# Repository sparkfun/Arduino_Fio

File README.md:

Arduino Fio
========================================

[*Arduino Fio (DEV-10116)*](https://www.sparkfun.com/products/10116)

Repository Contents
-------------------
* **/Hardware** - Eagle design files (.brd, .sch)
* **/Production** - Production panel files (.brd)

License Information
-------------------

This product is _**open source**_! 

Please review the LICENSE.md file for license information. 

If you have any questions or concerns on licensing, please contact techsupport@sparkfun.com.

Distributed as-is; no warranty is given.

- Your friends at SparkFun.

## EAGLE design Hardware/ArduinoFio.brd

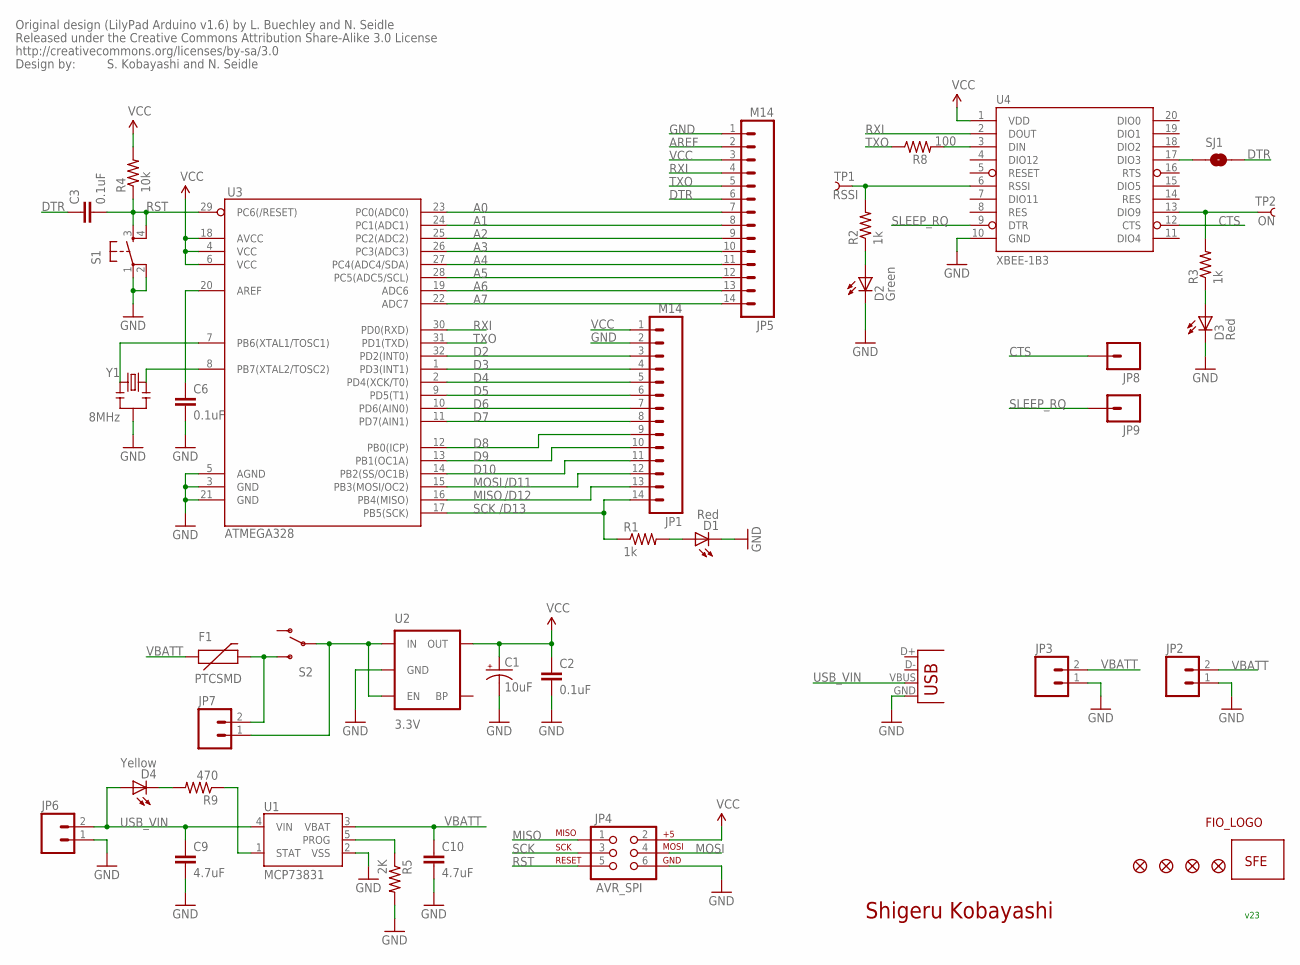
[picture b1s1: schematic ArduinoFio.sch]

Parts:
C1: 10uF; EIA3216
C2, C3, C6: 0.1uF; 0402-CAP
C9, C10: 4.7uF; 0402-CAP
D1, D3: Red; LED-0603
D2: Green; LED-0603
D4: Yellow; LED-0603
F1: PTCSMD; PTC-1206
FD1, FD2: FIDUCIAL1X2; FIDUCIAL-1X2
JP1, JP5: M14; 1X14
JP2, JP6, JP7: M02PTH; 1X02
JP3: M02-JST-2MM-SMT; JST-2-SMD
JP4: AVR_SPI; 2X3
JP8, JP9: M01PTH; 1X01
R1, R2, R3: 1k; 0402-RES
R4: 10k; 0402-RES
R5: 2K; 0402-RES
R8: 100; 0402-RES
R9: 470; 0402-RES
S1: TAC_SWITCHSMD; TACTILE_SWITCH_SMD
S2: SWITCH-SPSTSMD; AYZ0202
SJ1: SOLDERJUMPERNC; SJ_2S
TP1: RSSI; PAD.03X.05
TP2: ON; PAD.03X.05
U1: MCP73831; SOT23-5
U2: 3.3V; SOT23-5
U3: ATMEGA328; TQFP32-08
U4: XBEE-1B3; XBEE-SMD
U$1: LOGO-SFENEW; SFE-NEW-WEBLOGO
U$3: CREATIVE_COMMONS
U$4, U$5: FIDUCIAL1X2; FIDUCIAL-1X2
U$6: FIO_LOGOV2; FUNNEL_LOGO_BOTTOM_V2
X1: USBSMD; USB-MINIB
Y1: 8MHz; RESONATOR-SMD

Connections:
A0: JP5.7, U3.23 (PC0(ADC0))
A1: JP5.8, U3.24 (PC1(ADC1))
A2: JP5.9, U3.25 (PC2(ADC2))
A3: JP5.10, U3.26 (PC3(ADC3))
A4: JP5.11, U3.27 (PC4(ADC4/SDA))
A5: JP5.12, U3.28 (PC5(ADC5/SCL))
A6: JP5.13, U3.19 (ADC6)
A7: JP5.14, U3.22 (ADC7)
AREF: C6.1, JP5.2, U3.20 (AREF)
CTS: JP8.1, U4.12 (CTS)
D2: JP1.3, U3.32 (PD2(INT0))
D3: JP1.4, U3.1 (PD3(INT1))
D4: JP1.5, U3.2 (PD4(XCK/T0))
D5: JP1.6, U3.9 (PD5(T1))
D6: JP1.7, U3.10 (PD6(AIN0))
D7: JP1.8, U3.11 (PD7(AIN1))
D8: JP1.9, U3.12 (PB0(ICP))
D9: JP1.10, U3.13 (PB1(OC1A))
D10: JP1.11, U3.14 (PB2(SS/OC1B))
DTR: C3.1, JP5.6, SJ1.2
GND: C1.C (-), C2.2, C6.2, C9.2, C10.2, D1.C, D2.C, D3.C, JP1.2, JP2.1, JP3.1, JP4.6, JP5.1, JP6.1, R5.2, S1.1, S1.2, U1.2 (VSS), U2.2 (GND), U3.3 (GND), U3.5 (AGND), U3.21 (GND), U4.10 (GND), X1.GND, Y1.2
MISO: JP1.13, JP4.1, U3.16 (PB4(MISO))
MOSI: JP1.12, JP4.4, U3.15 (PB3(MOSI/OC2))
unnamed: R3.2, TP2.P$1, U4.13 (DIO9)
unnamed: D1.A, R1.2
unnamed: D2.A, R2.1
unnamed: R2.2, TP1.P$1, U4.6 (RSSI)
unnamed: JP7.1, S2.2, U2.1 (IN), U2.3 (EN)
unnamed: D3.A, R3.1
unnamed: R8.2, U4.3 (DIN)
unnamed: D4.C, R9.2
unnamed: F1.2, JP7.2, S2.3 (S)
unnamed: U3.7 (PB6(XTAL1/TOSC1)), Y1.3
unnamed: R5.1, U1.5 (PROG)
unnamed: U3.8 (PB7(XTAL2/TOSC2)), Y1.1
unnamed: SJ1.1, U4.17 (DIO3)
unnamed: R9.1, U1.1 (STAT)
RST: C3.2, JP4.5, R4.1, S1.3, S1.4, U3.29 (PC6(/RESET))
RXI: JP5.4, U3.30 (PD0(RXD)), U4.2 (DOUT)
SCK: JP1.14, JP4.3, R1.1, U3.17 (PB5(SCK))
SLEEP_RQ: JP9.1, U4.9 (DTR)
TXO: JP5.5, R8.1, U3.31 (PD1(TXD))
USB_VIN: C9.1, D4.A, JP6.2, U1.4 (VIN), X1.VBUS
VBATT: C10.1, F1.1, JP2.2, JP3.2, U1.3 (VBAT)
VCC: C1.A (+), C2.1, JP1.1, JP4.2, JP5.3, R4.2, U2.5 (OUT), U3.4 (VCC), U3.6 (VCC), U3.18 (AVCC), U4.1 (VDD)

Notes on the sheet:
Shigeru Kobayashi
/D11
/D12
/D13
Original design (LilyPad Arduino v1.6) by L. Buechley and N. Seidle
S. Kobayashi and N. Seidle
v23

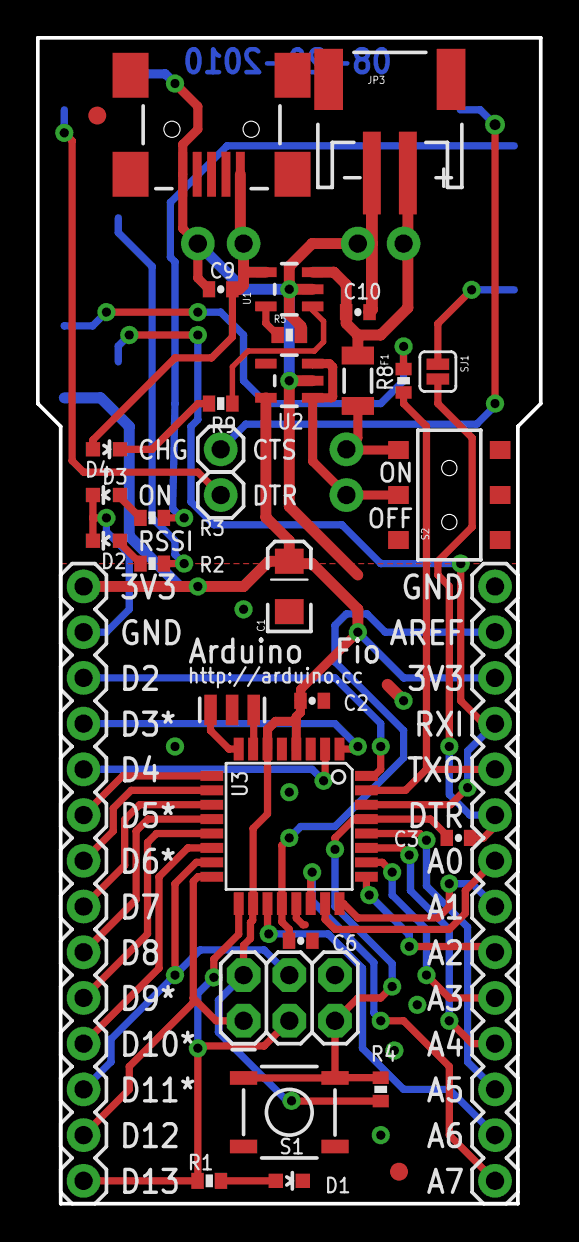
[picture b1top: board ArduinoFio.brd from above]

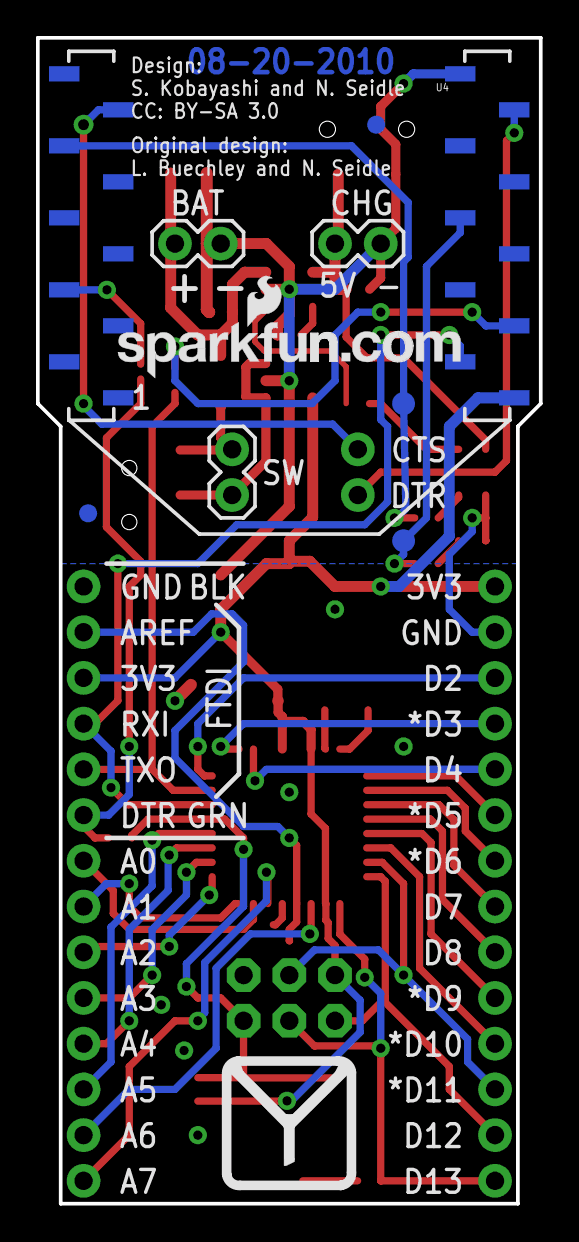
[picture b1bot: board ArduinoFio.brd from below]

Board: 2 copper layers, 27.9 x 64.8 mm, 45 parts (9 on the bottom side), 45 nets.

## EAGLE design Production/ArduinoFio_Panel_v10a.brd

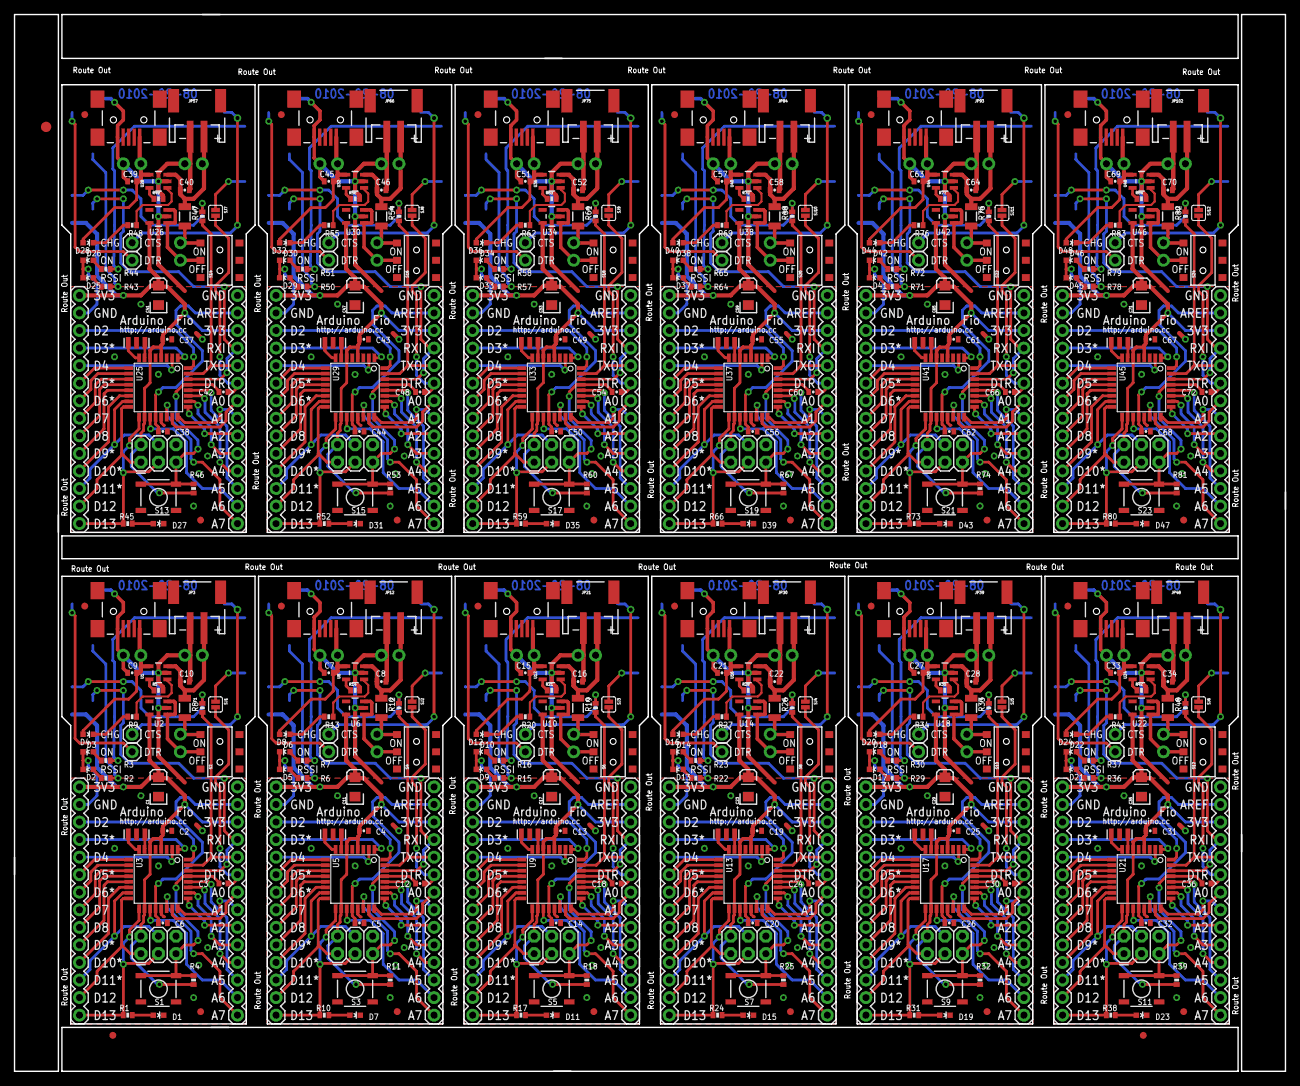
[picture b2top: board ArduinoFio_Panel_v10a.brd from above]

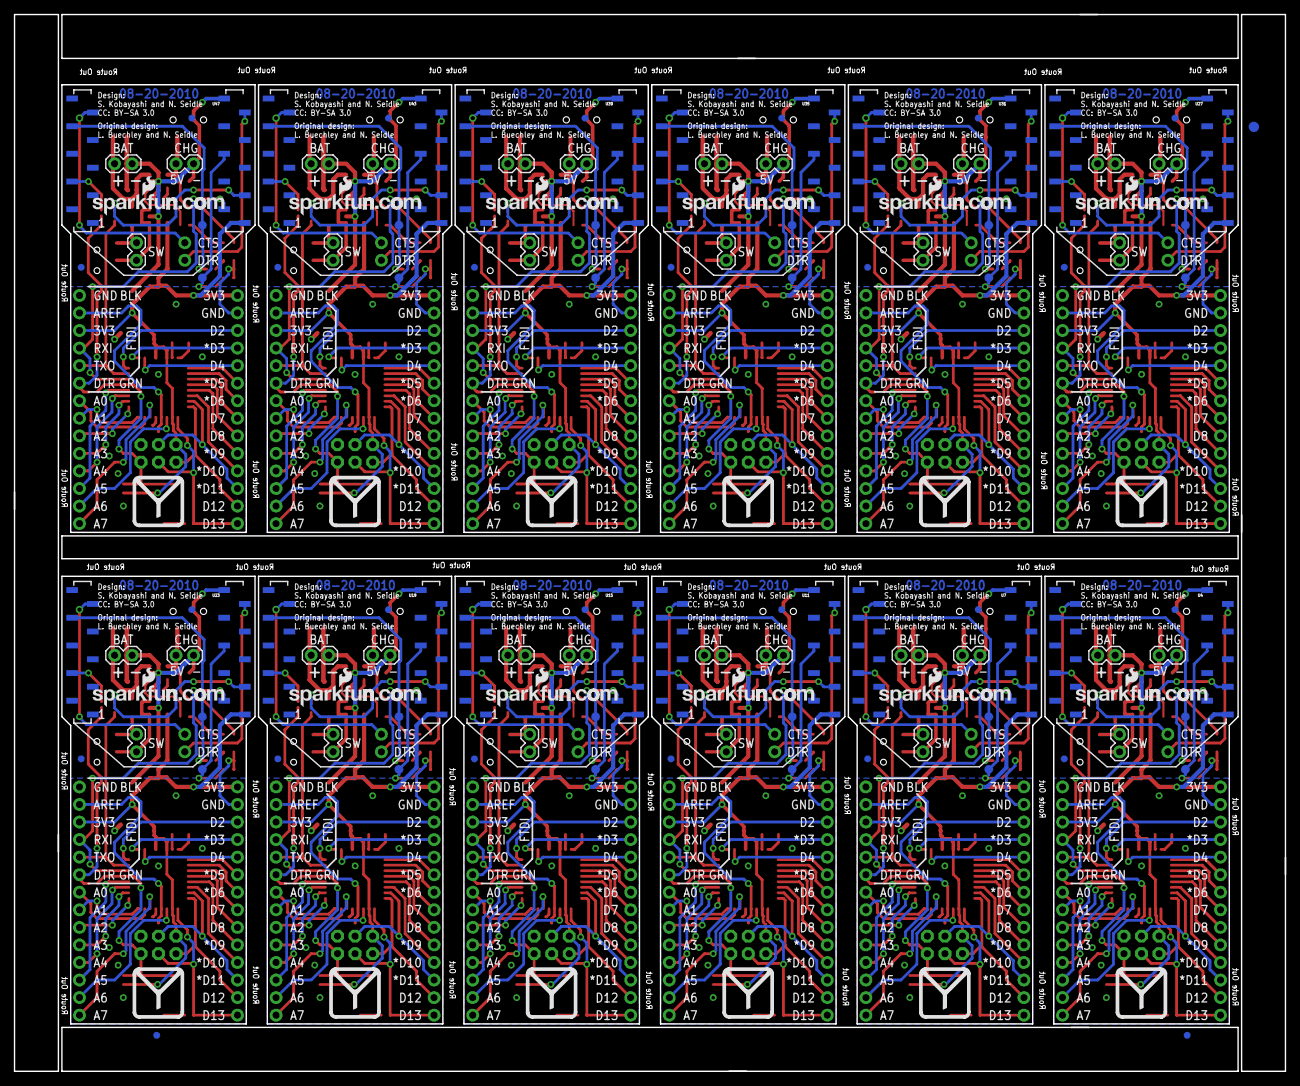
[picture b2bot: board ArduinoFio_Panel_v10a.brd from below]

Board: 2 copper layers, 183.9 x 152.9 mm, 534 parts (111 on the bottom side), 540 nets.

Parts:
C1, C11, C17, C23, C29, C35, C41, C47, C53, C59, C65, C71: 10uF; EIA3216
C2, C3, C4, C5, C6, C12, C13, C14, C18, C19, C20, C24, C25, C26, C30, C31, C32, C36, C37, C38, C42, C43, C44, C48, C49, C50, C54, C55, C56, C60, C61, C62, C66, C67, C68, C72: 0.1uF; 0402-CAP
C7, C8, C9, C10, C15, C16, C21, C22, C27, C28, C33, C34, C39, C40, C45, C46, C51, C52, C57, C58, C63, C64, C69, C70: 4.7uF; 0402-CAP
D1, D3, D6, D7, D10, D11, D14, D15, D18, D19, D22, D23, D26, D27, D30, D31, D34, D35, D38, D39, D42, D43, D46, D47: Red; LED-0603
D2, D5, D9, D13, D17, D21, D25, D29, D33, D37, D41, D45: Green; LED-0603
D4, D8, D12, D16, D20, D24, D28, D32, D36, D40, D44, D48: Yellow; LED-0603
E$1, E$2: FIDUCIAL-1.5X3
E$3, E$4, E$7, E$8: FIDUCIAL-1X2
F1, F2, F3, F4, F5, F6, F7, F8, F9, F10, F11, F12: PTCSMD; PTC-1206
FD1, FD2, FD3, FD4, FD5, FD6, FD7, FD8, FD9, FD10, FD11, FD12, FD13, FD14, FD15, FD16, FD17, FD18, FD19, FD20, FD21, FD22, FD23, FD24: FIDUCIAL1X2; FIDUCIAL-1X2
JP1, JP5, JP11, JP13, JP20, JP22, JP29, JP31, JP38, JP40, JP47, JP49, JP56, JP58, JP65, JP67, JP74, JP76, JP83, JP85, JP92, JP94, JP101, JP103: M14; 1X14
JP2, JP6, JP7, JP14, JP15, JP16, JP23, JP24, JP25, JP32, JP33, JP34, JP41, JP42, JP43, JP50, JP51, JP52, JP59, JP60, JP61, JP68, JP69, JP70, JP77, JP78, JP79, JP86, JP87, JP88, JP95, JP96, JP97, JP104, JP105, JP106: 1X02
JP3, JP12, JP21, JP30, JP39, JP48, JP57, JP66, JP75, JP84, JP93, JP102: JST-2-SMD
JP4, JP10, JP19, JP28, JP37, JP46, JP55, JP64, JP73, JP82, JP91, JP100: AVR_SPI; 2X3
JP8, JP9, JP17, JP18, JP26, JP27, JP35, JP36, JP44, JP45, JP53, JP54, JP62, JP63, JP71, JP72, JP80, JP81, JP89, JP90, JP98, JP99, JP107, JP108: 1X01
R1, R2, R3, R6, R7, R10, R15, R16, R17, R22, R23, R24, R29, R30, R31, R36, R37, R38, R43, R44, R45, R50, R51, R52, R57, R58, R59, R64, R65, R66, R71, R72, R73, R78, R79, R80: 1k; 0402-RES
R4, R11, R18, R25, R32, R39, R46, R53, R60, R67, R74, R81: 10k; 0402-RES
R5, R14, R21, R28, R35, R42, R49, R56, R63, R70, R77, R84: 2K; 0402-RES
R8, R12, R19, R26, R33, R40, R47, R54, R61, R68, R75, R82: 100; 0402-RES
R9, R13, R20, R27, R34, R41, R48, R55, R62, R69, R76, R83: 470; 0402-RES
S1, S3, S5, S7, S9, S11, S13, S15, S17, S19, S21, S23: TACTILE_SWITCH_SMD
S2, S4, S6, S8, S10, S12, S14, S16, S18, S20, S22, S24: AYZ0202
SJ1, SJ2, SJ3, SJ4, SJ5, SJ6, SJ7, SJ8, SJ9, SJ10, SJ11, SJ12: SOLDERJUMPERNC; SJ_2S
TP1, TP3, TP5, TP7, TP9, TP11, TP13, TP15, TP17, TP19, TP21, TP23: RSSI; PAD.03X.05
TP2, TP4, TP6, TP8, TP10, TP12, TP14, TP16, TP18, TP20, TP22, TP24: ON; PAD.03X.05
U1, U8, U12, U16, U20, U24, U28, U32, U36, U40, U44, U48: MCP73831; SOT23-5
U2, U6, U10, U14, U18, U22, U26, U30, U34, U38, U42, U46: 3.3V; SOT23-5
U3, U5, U9, U13, U17, U21, U25, U29, U33, U37, U41, U45: ATMEGA328; TQFP32-08
U4, U7, U11, U15, U19, U23, U27, U31, U35, U39, U43, U47: XBEE-1B3; XBEE-SMD
U$1, U$2, U$9, U$13, U$17, U$21, U$25, U$29, U$33, U$37, U$41, U$45: LOGO-SFENEW; SFE-NEW-WEBLOGO
U$3, U$4, U$5, U$7, U$10, U$11, U$14, U$15, U$18, U$19, U$22, U$23, U$26, U$27, U$30, U$31, U$34, U$35, U$38, U$39, U$42, U$43, U$46, U$47: FIDUCIAL1X2; FIDUCIAL-1X2
U$6, U$8, U$12, U$16, U$20, U$24, U$28, U$32, U$36, U$40, U$44, U$48: FIO_LOGOV2; FUNNEL_LOGO_BOTTOM_V2
X1, X2, X3, X4, X5, X6, X7, X8, X9, X10, X11, X12: USBSMD; USB-MINIB
Y1, Y2, Y3, Y4, Y5, Y6, Y7, Y8, Y9, Y10, Y11, Y12: 8MHz; RESONATOR-SMD

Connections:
A0: JP5.7, U3.23
A1: JP5.8, U3.24
A2: JP5.9, U3.25
A3: JP5.10, U3.26
A4: JP5.11, U3.27
A5: JP5.12, U3.28
A6: JP5.13, U3.19
A7: JP5.14, U3.22
A8: JP13.7, U5.23
A9: JP13.8, U5.24
A10: JP13.9, U5.25
A11: JP13.10, U5.26
A12: JP13.11, U5.27
A13: JP13.12, U5.28
A14: JP13.13, U5.19
A15: JP13.14, U5.22
A16: JP22.7, U9.23
A17: JP22.8, U9.24
A18: JP22.9, U9.25
A19: JP22.10, U9.26
A20: JP22.11, U9.27
A21: JP22.12, U9.28
A22: JP22.13, U9.19
A23: JP22.14, U9.22
A24: JP31.7, U13.23
A25: JP31.8, U13.24
A26: JP31.9, U13.25
A27: JP31.10, U13.26
A28: JP31.11, U13.27
A29: JP31.12, U13.28
A30: JP31.13, U13.19
A31: JP31.14, U13.22
A32: JP40.7, U17.23
A33: JP40.8, U17.24
A34: JP40.9, U17.25
A35: JP40.10, U17.26
A36: JP40.11, U17.27
A37: JP40.12, U17.28
A38: JP40.13, U17.19
A39: JP40.14, U17.22
A40: JP49.7, U21.23
A41: JP49.8, U21.24
A42: JP49.9, U21.25
A43: JP49.10, U21.26
A44: JP49.11, U21.27
A45: JP49.12, U21.28
A46: JP49.13, U21.19
A47: JP49.14, U21.22
A48: JP58.7, U25.23
A49: JP58.8, U25.24
A50: JP58.9, U25.25
A51: JP58.10, U25.26
A52: JP58.11, U25.27
A53: JP58.12, U25.28
A54: JP58.13, U25.19
A55: JP58.14, U25.22
A56: JP67.7, U29.23
A57: JP67.8, U29.24
A58: JP67.9, U29.25
A59: JP67.10, U29.26
A60: JP67.11, U29.27
A61: JP67.12, U29.28
A62: JP67.13, U29.19
A63: JP67.14, U29.22
A64: JP76.7, U33.23
A65: JP76.8, U33.24
A66: JP76.9, U33.25
A67: JP76.10, U33.26
A68: JP76.11, U33.27
A69: JP76.12, U33.28
A70: JP76.13, U33.19
A71: JP76.14, U33.22
A72: JP85.7, U37.23
A73: JP85.8, U37.24
A74: JP85.9, U37.25
A75: JP85.10, U37.26
A76: JP85.11, U37.27
A77: JP85.12, U37.28
A78: JP85.13, U37.19
A79: JP85.14, U37.22
A80: JP94.7, U41.23
A81: JP94.8, U41.24
A82: JP94.9, U41.25
A83: JP94.10, U41.26
A84: JP94.11, U41.27
A85: JP94.12, U41.28
A86: JP94.13, U41.19
A87: JP94.14, U41.22
A88: JP103.7, U45.23
A89: JP103.8, U45.24
A90: JP103.9, U45.25
A91: JP103.10, U45.26
A92: JP103.11, U45.27
A93: JP103.12, U45.28
A94: JP103.13, U45.19
A95: JP103.14, U45.22
AREF: C6.1, JP5.2, U3.20
AREF1: C5.1, JP13.2, U5.20
AREF2: C14.1, JP22.2, U9.20
AREF3: C20.1, JP31.2, U13.20
AREF4: C26.1, JP40.2, U17.20
AREF5: C32.1, JP49.2, U21.20
AREF6: C38.1, JP58.2, U25.20
AREF7: C44.1, JP67.2, U29.20
AREF8: C50.1, JP76.2, U33.20
AREF9: C56.1, JP85.2, U37.20
AREF10: C62.1, JP94.2, U41.20
AREF11: C68.1, JP103.2, U45.20
CTS: JP8.1, U4.12
CTS1: JP17.1, U7.12
CTS2: JP26.1, U11.12
CTS3: JP35.1, U15.12
CTS4: JP44.1, U19.12
CTS5: JP53.1, U23.12
CTS6: JP62.1, U27.12
CTS7: JP71.1, U31.12
CTS8: JP80.1, U35.12
CTS9: JP89.1, U39.12
CTS10: JP98.1, U43.12
CTS11: JP107.1, U47.12
D1: JP11.3, U5.32
D2: JP1.3, U3.32
D3: JP1.4, U3.1
D4: JP1.5, U3.2
D5: JP1.6, U3.9
D6: JP1.7, U3.10
D7: JP1.8, U3.11
D8: JP1.9, U3.12
D9: JP1.10, U3.13
D10: JP1.11, U3.14
D11: JP11.4, U5.1
D12: JP11.5, U5.2
D13: JP11.6, U5.9
D14: JP11.7, U5.10
D15: JP11.9, U5.12
D16: JP11.11, U5.14
D17: JP11.8, U5.11
D18: JP11.10, U5.13
D19: JP20.3, U9.32
D20: JP20.4, U9.1
D21: JP20.5, U9.2
D22: JP20.6, U9.9
D23: JP20.7, U9.10
D24: JP20.9, U9.12
D25: JP20.11, U9.14
D26: JP20.8, U9.11
D27: JP20.10, U9.13
D28: JP29.3, U13.32
D29: JP29.4, U13.1
D30: JP29.5, U13.2
D31: JP29.6, U13.9
D32: JP29.7, U13.10
D33: JP29.9, U13.12
D34: JP29.11, U13.14
D35: JP29.8, U13.11
D36: JP29.10, U13.13
D37: JP38.3, U17.32
D38: JP38.4, U17.1
D39: JP38.5, U17.2
D40: JP38.6, U17.9
D41: JP38.7, U17.10
D42: JP38.9, U17.12
D43: JP38.11, U17.14
D44: JP38.8, U17.11
D45: JP38.10, U17.13
D46: JP47.3, U21.32
D47: JP47.4, U21.1
D48: JP47.5, U21.2
D49: JP47.6, U21.9
D50: JP47.7, U21.10
D51: JP47.9, U21.12
D52: JP47.11, U21.14
D53: JP47.8, U21.11
D54: JP47.10, U21.13
D55: JP56.3, U25.32
D56: JP56.4, U25.1
D57: JP56.5, U25.2
D58: JP56.6, U25.9
D59: JP56.7, U25.10
D60: JP56.9, U25.12
D61: JP56.11, U25.14
D62: JP56.8, U25.11
D63: JP56.10, U25.13
D64: JP65.3, U29.32
D65: JP65.4, U29.1
D66: JP65.5, U29.2
D67: JP65.6, U29.9
D68: JP65.7, U29.10
D69: JP65.9, U29.12
D70: JP65.11, U29.14
D71: JP65.8, U29.11
D72: JP65.10, U29.13
D73: JP74.3, U33.32
D74: JP74.4, U33.1
D75: JP74.5, U33.2
D76: JP74.6, U33.9
D77: JP74.7, U33.10
D78: JP74.9, U33.12
D79: JP74.11, U33.14
D80: JP74.8, U33.11
D81: JP74.10, U33.13
D82: JP83.3, U37.32
D83: JP83.4, U37.1
D84: JP83.5, U37.2
D85: JP83.6, U37.9
D86: JP83.7, U37.10
D87: JP83.9, U37.12
D88: JP83.11, U37.14
D89: JP83.8, U37.11
D90: JP83.10, U37.13
D91: JP92.3, U41.32
D92: JP92.4, U41.1
D93: JP92.5, U41.2
D94: JP92.6, U41.9
D95: JP92.7, U41.10
D96: JP92.9, U41.12
D97: JP92.11, U41.14
D98: JP92.8, U41.11
D99: JP92.10, U41.13
D100: JP101.3, U45.32
D101: JP101.4, U45.1
D102: JP101.5, U45.2
D103: JP101.6, U45.9
D104: JP101.7, U45.10
D105: JP101.9, U45.12
D106: JP101.11, U45.14
D107: JP101.8, U45.11
D108: JP101.10, U45.13
DTR: C3.1, JP5.6, SJ1.2
DTR1: C12.1, JP13.6, SJ2.2
DTR2: C18.1, JP22.6, SJ3.2
DTR3: C24.1, JP31.6, SJ4.2
DTR4: C30.1, JP40.6, SJ5.2
DTR5: C36.1, JP49.6, SJ6.2
DTR6: C42.1, JP58.6, SJ7.2
DTR7: C48.1, JP67.6, SJ8.2
DTR8: C54.1, JP76.6, SJ9.2
DTR9: C60.1, JP85.6, SJ10.2
DTR10: C66.1, JP94.6, SJ11.2
DTR11: C72.1, JP103.6, SJ12.2
GND: C1.C, C2.2, C6.2, C9.2, C10.2, D1.C, D2.C, D3.C, JP1.2, JP2.1, JP3.1, JP4.6, JP5.1, JP6.1, R5.2, S1.1, S1.2, U1.2, U2.2, U3.3, U3.5, U3.21, U4.10, X1.GND, Y1.2
GND1: C4.2, C5.2, C7.2, C8.2, C11.C, D5.C, D6.C, D7.C, JP10.6, JP11.2, JP12.1, JP13.1, JP14.1, JP15.1, R14.2, S3.1, S3.2, U5.3, U5.5, U5.21, U6.2, U7.10, U8.2, X2.GND, Y2.2
GND2: C13.2, C14.2, C15.2, C16.2, C17.C, D9.C, D10.C, D11.C, JP19.6, JP20.2, JP21.1, JP22.1, JP23.1, JP24.1, R21.2, S5.1, S5.2, U9.3, U9.5, U9.21, U10.2, U11.10, U12.2, X3.GND, Y3.2
GND3: C19.2, C20.2, C21.2, C22.2, C23.C, D13.C, D14.C, D15.C, JP28.6, JP29.2, JP30.1, JP31.1, JP32.1, JP33.1, R28.2, S7.1, S7.2, U13.3, U13.5, U13.21, U14.2, U15.10, U16.2, X4.GND, Y4.2
GND4: C25.2, C26.2, C27.2, C28.2, C29.C, D17.C, D18.C, D19.C, JP37.6, JP38.2, JP39.1, JP40.1, JP41.1, JP42.1, R35.2, S9.1, S9.2, U17.3, U17.5, U17.21, U18.2, U19.10, U20.2, X5.GND, Y5.2
GND5: C31.2, C32.2, C33.2, C34.2, C35.C, D21.C, D22.C, D23.C, JP46.6, JP47.2, JP48.1, JP49.1, JP50.1, JP51.1, R42.2, S11.1, S11.2, U21.3, U21.5, U21.21, U22.2, U23.10, U24.2, X6.GND, Y6.2
GND6: C37.2, C38.2, C39.2, C40.2, C41.C, D25.C, D26.C, D27.C, JP55.6, JP56.2, JP57.1, JP58.1, JP59.1, JP60.1, R49.2, S13.1, S13.2, U25.3, U25.5, U25.21, U26.2, U27.10, U28.2, X7.GND, Y7.2
GND7: C43.2, C44.2, C45.2, C46.2, C47.C, D29.C, D30.C, D31.C, JP64.6, JP65.2, JP66.1, JP67.1, JP68.1, JP69.1, R56.2, S15.1, S15.2, U29.3, U29.5, U29.21, U30.2, U31.10, U32.2, X8.GND, Y8.2
GND8: C49.2, C50.2, C51.2, C52.2, C53.C, D33.C, D34.C, D35.C, JP73.6, JP74.2, JP75.1, JP76.1, JP77.1, JP78.1, R63.2, S17.1, S17.2, U33.3, U33.5, U33.21, U34.2, U35.10, U36.2, X9.GND, Y9.2
GND9: C55.2, C56.2, C57.2, C58.2, C59.C, D37.C, D38.C, D39.C, JP82.6, JP83.2, JP84.1, JP85.1, JP86.1, JP87.1, R70.2, S19.1, S19.2, U37.3, U37.5, U37.21, U38.2, U39.10, U40.2, X10.GND, Y10.2
GND10: C61.2, C62.2, C63.2, C64.2, C65.C, D41.C, D42.C, D43.C, JP91.6, JP92.2, JP93.1, JP94.1, JP95.1, JP96.1, R77.2, S21.1, S21.2, U41.3, U41.5, U41.21, U42.2, U43.10, U44.2, X11.GND, Y11.2
GND11: C67.2, C68.2, C69.2, C70.2, C71.C, D45.C, D46.C, D47.C, JP100.6, JP101.2, JP102.1, JP103.1, JP104.1, JP105.1, R84.2, S23.1, S23.2, U45.3, U45.5, U45.21, U46.2, U47.10, U48.2, X12.GND, Y12.2
MISO: JP1.13, JP4.1, U3.16
MISO1: JP10.1, JP11.13, U5.16
MISO2: JP19.1, JP20.13, U9.16
MISO3: JP28.1, JP29.13, U13.16
MISO4: JP37.1, JP38.13, U17.16
MISO5: JP46.1, JP47.13, U21.16
MISO6: JP55.1, JP56.13, U25.16
MISO7: JP64.1, JP65.13, U29.16
MISO8: JP73.1, JP74.13, U33.16
MISO9: JP82.1, JP83.13, U37.16
MISO10: JP91.1, JP92.13, U41.16
MISO11: JP100.1, JP101.13, U45.16
MOSI: JP1.12, JP4.4, U3.15
MOSI1: JP10.4, JP11.12, U5.15
MOSI2: JP19.4, JP20.12, U9.15
MOSI3: JP28.4, JP29.12, U13.15
MOSI4: JP37.4, JP38.12, U17.15
MOSI5: JP46.4, JP47.12, U21.15
MOSI6: JP55.4, JP56.12, U25.15
MOSI7: JP64.4, JP65.12, U29.15
MOSI8: JP73.4, JP74.12, U33.15
MOSI9: JP82.4, JP83.12, U37.15
MOSI10: JP91.4, JP92.12, U41.15
MOSI11: JP100.4, JP101.12, U45.15
unnamed: R3.2, TP2.P$1, U4.13
unnamed: D1.A, R1.2
unnamed: D2.A, R2.1
unnamed: R2.2, TP1.P$1, U4.6
unnamed: JP7.1, S2.2, U2.1, U2.3
unnamed: D3.A, R3.1
unnamed: R8.2, U4.3
unnamed: D4.C, R9.2
unnamed: F1.2, JP7.2, S2.3
unnamed: U3.7, Y1.3
unnamed: R5.1, U1.5
unnamed: U3.8, Y1.1
unnamed: SJ1.1, U4.17
unnamed: R9.1, U1.1
unnamed: D5.A, R6.1
unnamed: R6.2, TP3.P$1, U7.6
unnamed: D6.A, R7.1
unnamed: R7.2, TP4.P$1, U7.13
unnamed: U5.7, Y2.3
unnamed: U5.8, Y2.1
unnamed: D7.A, R10.2
unnamed: R12.2, U7.3
unnamed: JP16.1, S4.2, U6.1, U6.3
unnamed: F2.2, JP16.2, S4.3
unnamed: SJ2.1, U7.17
unnamed: R14.1, U8.5
unnamed: R13.1, U8.1
unnamed: D8.C, R13.2
unnamed: D9.A, R15.1
unnamed: R15.2, TP5.P$1, U11.6
unnamed: D10.A, R16.1
unnamed: R16.2, TP6.P$1, U11.13
unnamed: U9.7, Y3.3
unnamed: U9.8, Y3.1
unnamed: D11.A, R17.2
unnamed: R19.2, U11.3
unnamed: JP25.1, S6.2, U10.1, U10.3
unnamed: F3.2, JP25.2, S6.3
unnamed: SJ3.1, U11.17
unnamed: R21.1, U12.5
unnamed: R20.1, U12.1
unnamed: D12.C, R20.2
unnamed: D13.A, R22.1
unnamed: R22.2, TP7.P$1, U15.6
unnamed: D14.A, R23.1
unnamed: R23.2, TP8.P$1, U15.13
unnamed: U13.7, Y4.3
unnamed: U13.8, Y4.1
unnamed: D15.A, R24.2
unnamed: R26.2, U15.3
unnamed: JP34.1, S8.2, U14.1, U14.3
unnamed: F4.2, JP34.2, S8.3
unnamed: SJ4.1, U15.17
unnamed: R28.1, U16.5
unnamed: R27.1, U16.1
unnamed: D16.C, R27.2
unnamed: D17.A, R29.1
unnamed: R29.2, TP9.P$1, U19.6
unnamed: D18.A, R30.1
unnamed: R30.2, TP10.P$1, U19.13
unnamed: U17.7, Y5.3
unnamed: U17.8, Y5.1
unnamed: D19.A, R31.2
unnamed: R33.2, U19.3
unnamed: JP43.1, S10.2, U18.1, U18.3
unnamed: F5.2, JP43.2, S10.3
unnamed: SJ5.1, U19.17
unnamed: R35.1, U20.5
unnamed: R34.1, U20.1
unnamed: D20.C, R34.2
unnamed: D21.A, R36.1
unnamed: R36.2, TP11.P$1, U23.6
unnamed: D22.A, R37.1
unnamed: R37.2, TP12.P$1, U23.13
unnamed: U21.7, Y6.3
unnamed: U21.8, Y6.1
unnamed: D23.A, R38.2
unnamed: R40.2, U23.3
unnamed: JP52.1, S12.2, U22.1, U22.3
unnamed: F6.2, JP52.2, S12.3
unnamed: SJ6.1, U23.17
unnamed: R42.1, U24.5
unnamed: R41.1, U24.1
unnamed: D24.C, R41.2
unnamed: D25.A, R43.1
unnamed: R43.2, TP13.P$1, U27.6
unnamed: D26.A, R44.1
unnamed: R44.2, TP14.P$1, U27.13
unnamed: U25.7, Y7.3
unnamed: U25.8, Y7.1
unnamed: D27.A, R45.2
unnamed: R47.2, U27.3
unnamed: JP61.1, S14.2, U26.1, U26.3
unnamed: F7.2, JP61.2, S14.3
unnamed: SJ7.1, U27.17
unnamed: R49.1, U28.5
unnamed: R48.1, U28.1
unnamed: D28.C, R48.2
unnamed: D29.A, R50.1
unnamed: R50.2, TP15.P$1, U31.6
unnamed: D30.A, R51.1
unnamed: R51.2, TP16.P$1, U31.13
unnamed: U29.7, Y8.3
unnamed: U29.8, Y8.1
unnamed: D31.A, R52.2
unnamed: R54.2, U31.3
unnamed: JP70.1, S16.2, U30.1, U30.3
unnamed: F8.2, JP70.2, S16.3
unnamed: SJ8.1, U31.17
unnamed: R56.1, U32.5
unnamed: R55.1, U32.1
unnamed: D32.C, R55.2
unnamed: D33.A, R57.1
unnamed: R57.2, TP17.P$1, U35.6
unnamed: D34.A, R58.1
unnamed: R58.2, TP18.P$1, U35.13
unnamed: U33.7, Y9.3
unnamed: U33.8, Y9.1
unnamed: D35.A, R59.2
unnamed: R61.2, U35.3
unnamed: JP79.1, S18.2, U34.1, U34.3
unnamed: F9.2, JP79.2, S18.3
unnamed: SJ9.1, U35.17
unnamed: R63.1, U36.5
unnamed: R62.1, U36.1
unnamed: D36.C, R62.2
unnamed: D37.A, R64.1
unnamed: R64.2, TP19.P$1, U39.6
unnamed: D38.A, R65.1
unnamed: R65.2, TP20.P$1, U39.13
unnamed: U37.7, Y10.3
unnamed: U37.8, Y10.1
unnamed: D39.A, R66.2
unnamed: R68.2, U39.3
unnamed: JP88.1, S20.2, U38.1, U38.3
unnamed: F10.2, JP88.2, S20.3
unnamed: SJ10.1, U39.17
unnamed: R70.1, U40.5
unnamed: R69.1, U40.1
unnamed: D40.C, R69.2
unnamed: D41.A, R71.1
unnamed: R71.2, TP21.P$1, U43.6
unnamed: D42.A, R72.1
unnamed: R72.2, TP22.P$1, U43.13
unnamed: U41.7, Y11.3
unnamed: U41.8, Y11.1
unnamed: D43.A, R73.2
unnamed: R75.2, U43.3
unnamed: JP97.1, S22.2, U42.1, U42.3
unnamed: F11.2, JP97.2, S22.3
unnamed: SJ11.1, U43.17
unnamed: R77.1, U44.5
unnamed: R76.1, U44.1
unnamed: D44.C, R76.2
unnamed: D45.A, R78.1
unnamed: R78.2, TP23.P$1, U47.6
unnamed: D46.A, R79.1
unnamed: R79.2, TP24.P$1, U47.13
unnamed: U45.7, Y12.3
unnamed: U45.8, Y12.1
unnamed: D47.A, R80.2
unnamed: R82.2, U47.3
unnamed: JP106.1, S24.2, U46.1, U46.3
unnamed: F12.2, JP106.2, S24.3
unnamed: SJ12.1, U47.17
unnamed: R84.1, U48.5
unnamed: R83.1, U48.1
unnamed: D48.C, R83.2
RST: C3.2, JP4.5, R4.1, S1.3, S1.4, U3.29
RST1: C12.2, JP10.5, R11.1, S3.3, S3.4, U5.29
RST2: C18.2, JP19.5, R18.1, S5.3, S5.4, U9.29
RST3: C24.2, JP28.5, R25.1, S7.3, S7.4, U13.29
RST4: C30.2, JP37.5, R32.1, S9.3, S9.4, U17.29
RST5: C36.2, JP46.5, R39.1, S11.3, S11.4, U21.29
RST6: C42.2, JP55.5, R46.1, S13.3, S13.4, U25.29
RST7: C48.2, JP64.5, R53.1, S15.3, S15.4, U29.29
RST8: C54.2, JP73.5, R60.1, S17.3, S17.4, U33.29
RST9: C60.2, JP82.5, R67.1, S19.3, S19.4, U37.29
RST10: C66.2, JP91.5, R74.1, S21.3, S21.4, U41.29
RST11: C72.2, JP100.5, R81.1, S23.3, S23.4, U45.29
RXI: JP5.4, U3.30, U4.2
RXI1: JP13.4, U5.30, U7.2
RXI2: JP22.4, U9.30, U11.2
RXI3: JP31.4, U13.30, U15.2
RXI4: JP40.4, U17.30, U19.2
RXI5: JP49.4, U21.30, U23.2
RXI6: JP58.4, U25.30, U27.2
RXI7: JP67.4, U29.30, U31.2
RXI8: JP76.4, U33.30, U35.2
RXI9: JP85.4, U37.30, U39.2
RXI10: JP94.4, U41.30, U43.2
RXI11: JP103.4, U45.30, U47.2
SCK: JP1.14, JP4.3, R1.1, U3.17
SCK1: JP10.3, JP11.14, R10.1, U5.17
SCK2: JP19.3, JP20.14, R17.1, U9.17
SCK3: JP28.3, JP29.14, R24.1, U13.17
SCK4: JP37.3, JP38.14, R31.1, U17.17
SCK5: JP46.3, JP47.14, R38.1, U21.17
SCK6: JP55.3, JP56.14, R45.1, U25.17
SCK7: JP64.3, JP65.14, R52.1, U29.17
SCK8: JP73.3, JP74.14, R59.1, U33.17
SCK9: JP82.3, JP83.14, R66.1, U37.17
SCK10: JP91.3, JP92.14, R73.1, U41.17
SCK11: JP100.3, JP101.14, R80.1, U45.17
SLEEP_RQ: JP9.1, U4.9
SLEEP_RQ1: JP18.1, U7.9
SLEEP_RQ2: JP27.1, U11.9
SLEEP_RQ3: JP36.1, U15.9
SLEEP_RQ4: JP45.1, U19.9
SLEEP_RQ5: JP54.1, U23.9
SLEEP_RQ6: JP63.1, U27.9
SLEEP_RQ7: JP72.1, U31.9
SLEEP_RQ8: JP81.1, U35.9
SLEEP_RQ9: JP90.1, U39.9
SLEEP_RQ10: JP99.1, U43.9
SLEEP_RQ11: JP108.1, U47.9
TXO: JP5.5, R8.1, U3.31
TXO1: JP13.5, R12.1, U5.31
TXO2: JP22.5, R19.1, U9.31
TXO3: JP31.5, R26.1, U13.31
TXO4: JP40.5, R33.1, U17.31
TXO5: JP49.5, R40.1, U21.31
TXO6: JP58.5, R47.1, U25.31
TXO7: JP67.5, R54.1, U29.31
TXO8: JP76.5, R61.1, U33.31
TXO9: JP85.5, R68.1, U37.31
TXO10: JP94.5, R75.1, U41.31
TXO11: JP103.5, R82.1, U45.31
USB_VIN: C9.1, D4.A, JP6.2, U1.4, X1.VBUS
USB_VIN1: C7.1, D8.A, JP15.2, U8.4, X2.VBUS
USB_VIN2: C15.1, D12.A, JP24.2, U12.4, X3.VBUS
USB_VIN3: C21.1, D16.A, JP33.2, U16.4, X4.VBUS
USB_VIN4: C27.1, D20.A, JP42.2, U20.4, X5.VBUS
USB_VIN5: C33.1, D24.A, JP51.2, U24.4, X6.VBUS
USB_VIN6: C39.1, D28.A, JP60.2, U28.4, X7.VBUS
USB_VIN7: C45.1, D32.A, JP69.2, U32.4, X8.VBUS
USB_VIN8: C51.1, D36.A, JP78.2, U36.4, X9.VBUS
USB_VIN9: C57.1, D40.A, JP87.2, U40.4, X10.VBUS
USB_VIN10: C63.1, D44.A, JP96.2, U44.4, X11.VBUS
USB_VIN11: C69.1, D48.A, JP105.2, U48.4, X12.VBUS
VBATT: C10.1, F1.1, JP2.2, JP3.2, U1.3
VBATT1: C8.1, F2.1, JP12.2, JP14.2, U8.3
VBATT2: C16.1, F3.1, JP21.2, JP23.2, U12.3
VBATT3: C22.1, F4.1, JP30.2, JP32.2, U16.3
VBATT4: C28.1, F5.1, JP39.2, JP41.2, U20.3
VBATT5: C34.1, F6.1, JP48.2, JP50.2, U24.3
VBATT6: C40.1, F7.1, JP57.2, JP59.2, U28.3
VBATT7: C46.1, F8.1, JP66.2, JP68.2, U32.3
VBATT8: C52.1, F9.1, JP75.2, JP77.2, U36.3
VBATT9: C58.1, F10.1, JP84.2, JP86.2, U40.3
VBATT10: C64.1, F11.1, JP93.2, JP95.2, U44.3
VBATT11: C70.1, F12.1, JP102.2, JP104.2, U48.3
VCC: C1.A, C2.1, JP1.1, JP4.2, JP5.3, R4.2, U2.5, U3.4, U3.6, U3.18, U4.1
VCC1: C4.1, C11.A, JP10.2, JP11.1, JP13.3, R11.2, U5.4, U5.6, U5.18, U6.5, U7.1
VCC2: C13.1, C17.A, JP19.2, JP20.1, JP22.3, R18.2, U9.4, U9.6, U9.18, U10.5, U11.1
VCC3: C19.1, C23.A, JP28.2, JP29.1, JP31.3, R25.2, U13.4, U13.6, U13.18, U14.5, U15.1
VCC4: C25.1, C29.A, JP37.2, JP38.1, JP40.3, R32.2, U17.4, U17.6, U17.18, U18.5, U19.1
VCC5: C31.1, C35.A, JP46.2, JP47.1, JP49.3, R39.2, U21.4, U21.6, U21.18, U22.5, U23.1
VCC6: C37.1, C41.A, JP55.2, JP56.1, JP58.3, R46.2, U25.4, U25.6, U25.18, U26.5, U27.1
VCC7: C43.1, C47.A, JP64.2, JP65.1, JP67.3, R53.2, U29.4, U29.6, U29.18, U30.5, U31.1
VCC8: C49.1, C53.A, JP73.2, JP74.1, JP76.3, R60.2, U33.4, U33.6, U33.18, U34.5, U35.1
VCC9: C55.1, C59.A, JP82.2, JP83.1, JP85.3, R67.2, U37.4, U37.6, U37.18, U38.5, U39.1
VCC10: C61.1, C65.A, JP91.2, JP92.1, JP94.3, R74.2, U41.4, U41.6, U41.18, U42.5, U43.1
VCC11: C67.1, C71.A, JP100.2, JP101.1, JP103.3, R81.2, U45.4, U45.6, U45.18, U46.5, U47.1

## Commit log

2015-10-06 Adding hardware files, updating readme
2016-03-02 added bottom side fiducials
2016-03-02 created new v10a panel

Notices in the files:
parts and their libraries:
SparkFun: Released under the Creative Commons Attribution Share-Alike 3.0 License
SparkFun: http://creativecommons.org/licenses/by-sa/3.0
SparkFun-Aesthetics: Licensing: Creative Commons ShareAlike 4.0 International - https://creativecommons.org/licenses/by-sa/4.0
